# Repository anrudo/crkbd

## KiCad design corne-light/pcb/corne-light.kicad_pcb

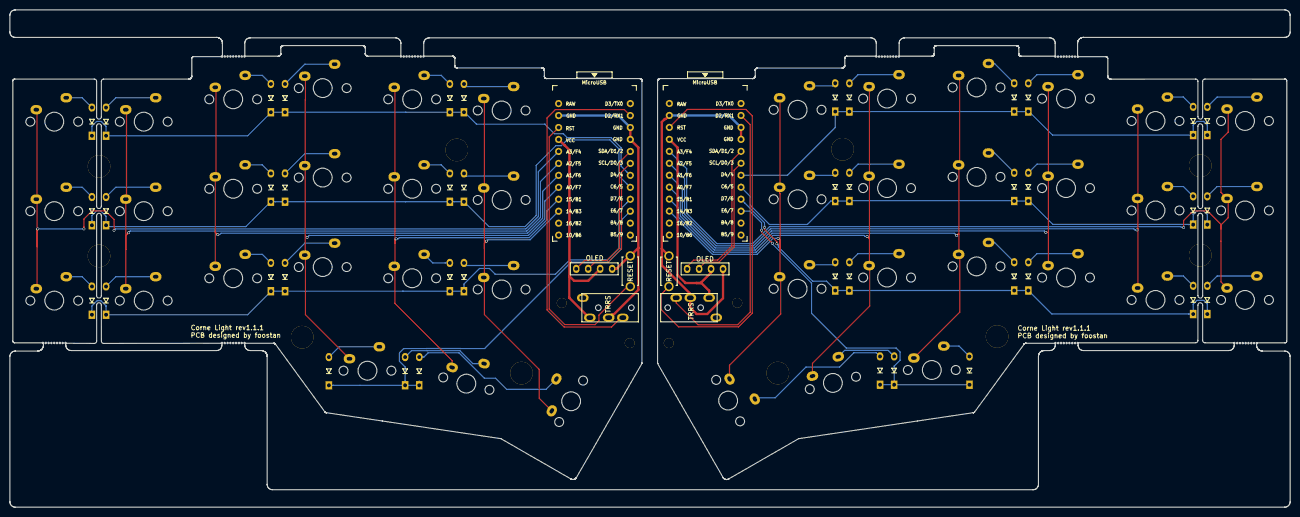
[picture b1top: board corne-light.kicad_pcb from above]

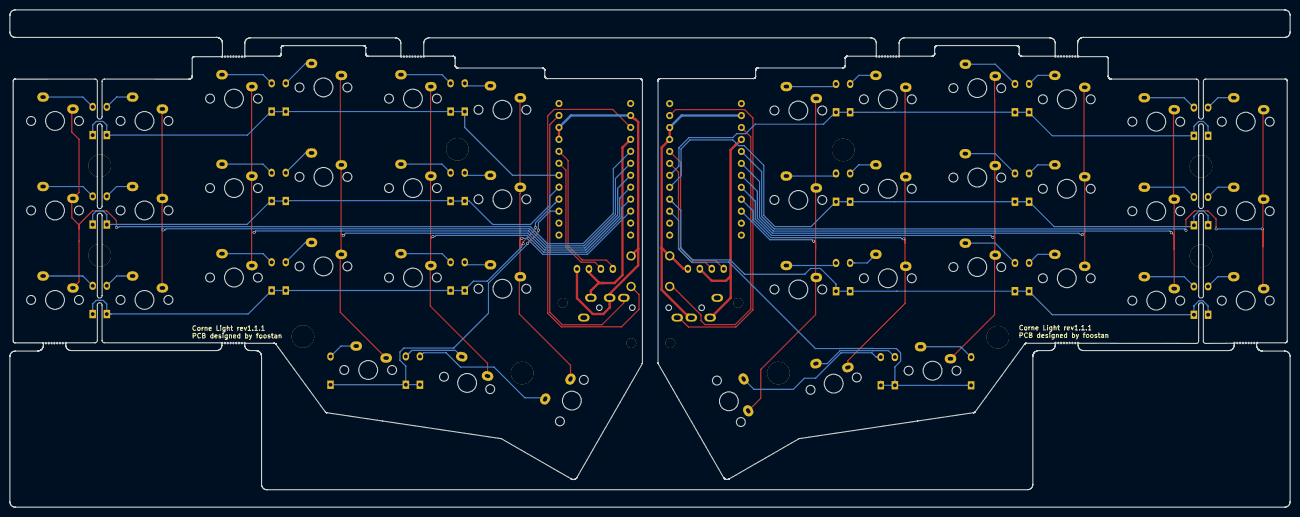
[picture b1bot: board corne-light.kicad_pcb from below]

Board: 2 copper layers, 271.8 x 105.6 mm, 114 parts (7 on the bottom side), 74 nets.

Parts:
D1, D2, D3, D4, D5, D6, D7, D8, D9, D10, D11, D12, D13, D14, D15, D16, D17, D18, D19, D20, D21, D22, D23, D24, D25, D26, D27, D28, D29, D30, D31, D32, D33, D34, D35, D36, D37, D38, D39, D40, D41, D42: D; D3_TH
J1, J6: MJ-4PP-9; MJ-4PP-9_1side
J2, J7: OLED; OLED_1side
J5, J5#2, J5#3, J5#4, J5#5, J5#6, J5#7, J5#8: Breakaway_Tabs; breakaway-mousebites
RSW1, RSW2: SW_PUSH; ResetSW_1side
Ref**: Val**; M2_Threads_v2
Ref**#2, Ref**#3, Ref**#4: Val**; M2_Threads_v2
Ref**#5, Ref**#6, Ref**#7, Ref**#8, Ref**#9, Ref**#10, Ref**#11, Ref**#12, Ref**#13, Ref**#14: Val**; M2_HOLE_v2
SW1, SW2, SW3, SW4, SW5, SW6, SW7, SW8, SW9, SW10, SW11, SW12, SW13, SW14, SW15, SW16, SW17, SW18, SW19, SW20, SW21, SW22, SW23, SW24, SW25, SW26, SW27, SW28, SW29, SW30, SW31, SW32, SW33, SW34, SW35, SW36, SW37, SW38, SW39, SW40, SW41, SW42: SW_PUSH; CherryMX_1u
U1, U2: ProMicro; ProMicro_v3

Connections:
GND: J1.C, J2.4, RSW1.2, U1.3, U1.4, U1.23
GNDA: J6.C, J7.1, RSW2.2, U2.3, U2.4, U2.23
unnamed: D1.2, SW1.2
unnamed: D2.2, SW2.2
unnamed: D3.2, SW3.2
unnamed: D4.2, SW4.2
unnamed: D5.2, SW5.2
unnamed: D6.2, SW6.2
unnamed: D7.2, SW7.2
unnamed: D8.2, SW8.2
unnamed: D9.2, SW9.2
unnamed: D10.2, SW10.2
unnamed: D11.2, SW11.2
unnamed: D12.2, SW12.2
unnamed: D13.2, SW13.2
unnamed: D14.2, SW14.2
unnamed: D15.2, SW15.2
unnamed: D16.2, SW16.2
unnamed: D17.2, SW17.2
unnamed: D18.2, SW18.2
unnamed: D19.2, SW19.2
unnamed: D20.2, SW20.2
unnamed: D21.2, SW21.2
unnamed: D22.2, SW22.2
unnamed: D23.2, SW23.2
unnamed: D24.2, SW24.2
unnamed: D25.2, SW25.2
unnamed: D26.2, SW26.2
unnamed: D27.2, SW27.2
unnamed: D28.2, SW28.2
unnamed: D29.2, SW29.2
unnamed: D30.2, SW30.2
unnamed: D31.2, SW31.2
unnamed: D32.2, SW32.2
unnamed: D33.2, SW33.2
unnamed: D34.2, SW34.2
unnamed: D35.2, SW35.2
unnamed: D36.2, SW36.2
unnamed: D37.2, SW37.2
unnamed: D38.2, SW38.2
unnamed: D39.2, SW39.2
unnamed: D40.2, SW40.2
unnamed: D41.2, SW41.2
unnamed: D42.2, SW42.2
SCL: J2.2, U1.6
SCL_r: J7.3, U2.6
SDA: J2.1, U1.5
SDA_r: J7.4, U2.5
VCC: J1.D, J2.3, U1.21
VDD: J6.D, J7.2, U2.21
col0: SW1.1, SW7.1, SW13.1, U1.20
col0_r: SW22.1, SW28.1, SW34.1, U2.20
col1: SW2.1, SW8.1, SW14.1, U1.19
col1_r: SW23.1, SW29.1, SW35.1, U2.19
col2: SW3.1, SW9.1, SW15.1, U1.18
col2_r: SW24.1, SW30.1, SW36.1, U2.18
col3: SW4.1, SW10.1, SW16.1, SW19.1, U1.17
col3_r: SW25.1, SW31.1, SW37.1, SW40.1, U2.17
col4: SW5.1, SW11.1, SW17.1, SW20.1, U1.16
col4_r: SW26.1, SW32.1, SW38.1, SW41.1, U2.16
col5: SW6.1, SW12.1, SW18.1, SW21.1, U1.15
col5_r: SW27.1, SW33.1, SW39.1, SW42.1, U2.15
data: J1.B, U1.2
data_r: J6.B, U2.2
reset: RSW1.1, U1.22
reset_r: RSW2.1, U2.22
row0: D1.1, D2.1, D3.1, D4.1, D5.1, D6.1, U1.7
row0_r: D22.1, D23.1, D24.1, D25.1, D26.1, D27.1, U2.7
row1: D7.1, D8.1, D9.1, D10.1, D11.1, D12.1, U1.8
row1_r: D28.1, D29.1, D30.1, D31.1, D32.1, D33.1, U2.8
row2: D13.1, D14.1, D15.1, D16.1, D17.1, D18.1, U1.9
row2_r: D34.1, D35.1, D36.1, D37.1, D38.1, D39.1, U2.9
row3: D19.1, D20.1, D21.1, U1.10
row3_r: D40.1, D41.1, D42.1, U2.10

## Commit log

2020-04-10 added long design to bottom pbc plate, cleaned up edge cut
